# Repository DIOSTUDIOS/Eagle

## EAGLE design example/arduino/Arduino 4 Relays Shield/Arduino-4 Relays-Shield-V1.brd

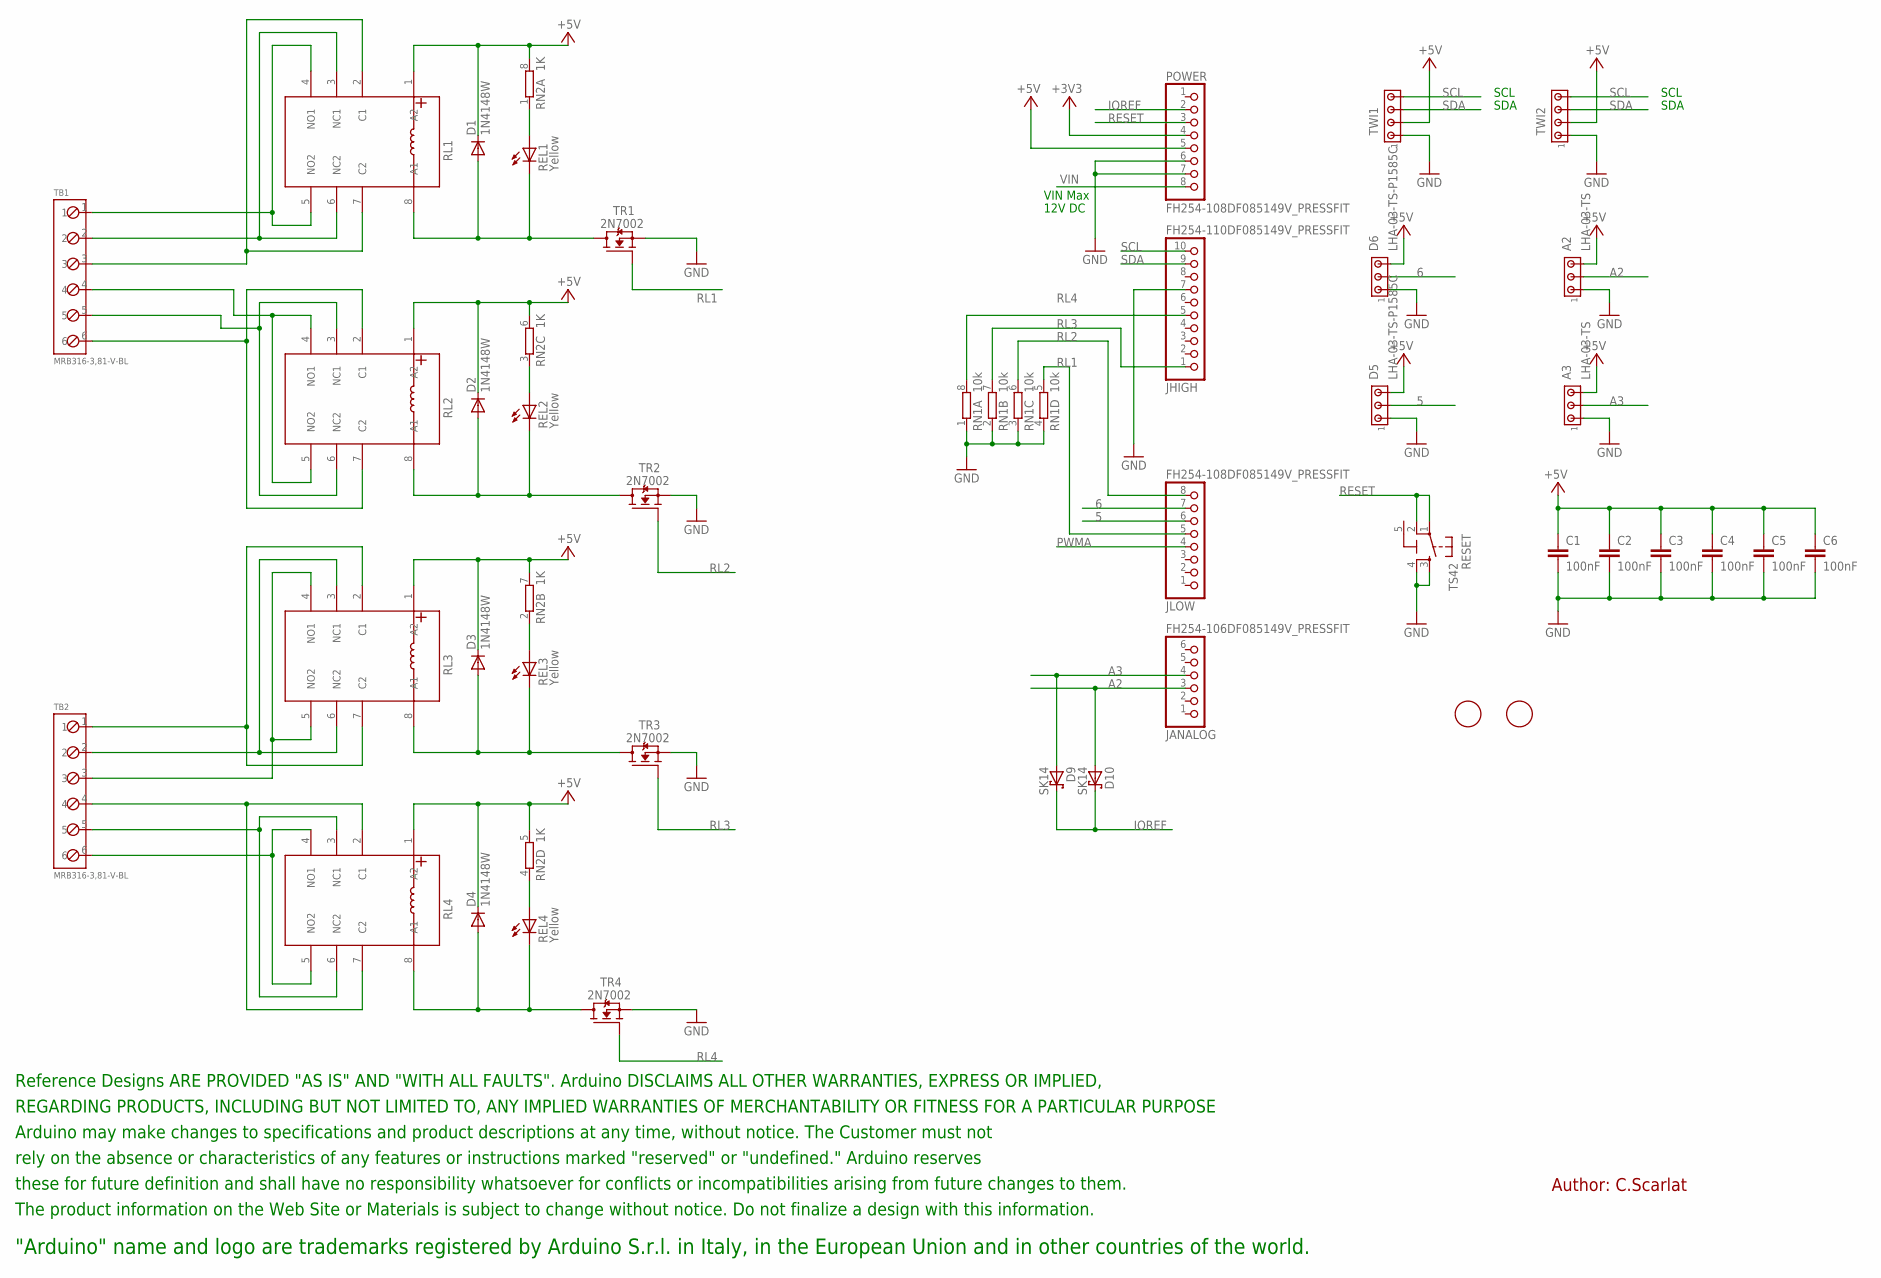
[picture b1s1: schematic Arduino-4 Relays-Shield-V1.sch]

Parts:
A2, A3: LHA-03-TS; 10X03MTA
C1, C2, C3, C4, C5, C6: 100nF; C0603-ROUND
D1, D2, D3, D4: 1N4148W; SOD123
D5, D6: LHA-03-TS-P1585C; 10X03MTA
D9, D10: SK14; SMB
FID2, FID3: FIDUCIALMOUNT; FIDUCIA-MOUNT
JANALOG: FH254-106DF085149V_PRESSFIT; 1X06-TH-PRESSFIT
JHIGH: FH254-110DF085149V_PRESSFIT; 1X10-TH-PRESSFIT
JLOW: FH254-108DF085149V_PRESSFIT; 1X08-TH-PRESSFIT
POWER: FH254-108DF085149V_PRESSFIT; 1X08-TH-PRESSFIT
REL1, REL2, REL3, REL4: Yellow; CHIPLED_0805
RESET: TS42
RL1, RL2, RL3, RL4: 1045_G5V-2-H1; RELE'-30SSERIES-DIL-2X
RN1: 10k; CAY16
RN2: 1K; CAY16
TB1, TB2: MRB316-3,81-V-BL
TR1, TR2, TR3, TR4: 2N7002; SOT-23
TWI1, TWI2: 0205_LHA-04-TS__4X1_VERTICALE_BIANCO_P_2,54; 10X04MTA
U$2: DISCLAIMER-SMALL; DISCLAIMER

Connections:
5: D5.2, JLOW.6
5-GND: RESET.5 (5-GND)
6: D6.2, JLOW.7
+3V3: POWER.4
+5V: A2.3, A3.3, C1.1, C2.1, C3.1, C4.1, C5.1, C6.1, D1.C, D2.C, D3.C, D4.C, D5.3, D6.3, POWER.5, RL1.1 (A2), RL2.1 (A2), RL3.1 (A2), RL4.1 (A2), RN2.5 (2), RN2.6 (2), RN2.7 (2), RN2.8 (2), TWI1.2, TWI2.2
A2: A2.2, D10.A, JANALOG.3
A3: A3.2, D9.A, JANALOG.4
GND: A2.1, A3.1, C1.2, C2.2, C3.2, C4.2, C5.2, C6.2, D5.1, D6.1, JHIGH.7, POWER.6, POWER.7, RESET.3, RESET.4, RN1.1, RN1.2 (1), RN1.3 (1), RN1.4 (1), TR1.2 (S), TR2.2 (S), TR3.2 (S), TR4.2 (S), TWI1.1, TWI2.1
IOREF: D9.C, D10.C, POWER.2
unnamed: REL1.A, RN2.1
unnamed: REL2.A, RN2.3 (1)
unnamed: REL3.A, RN2.2 (1)
unnamed: REL4.A, RN2.4 (1)
unnamed: D1.A, REL1.C, RL1.8 (A1), TR1.1 (D)
unnamed: D2.A, REL2.C, RL2.8 (A1), TR2.1 (D)
unnamed: D3.A, REL3.C, RL3.8 (A1), TR3.1 (D)
unnamed: D4.A, REL4.C, RL4.8 (A1), TR4.1 (D)
PWMA: JLOW.4
REL1_COM: RL1.2 (C1), RL1.7 (C2), TB1.3
REL1_NC: RL1.3 (NC1), RL1.6 (NC2), TB1.2
REL1_NO: RL1.4 (NO1), RL1.5 (NO2), TB1.1
REL2_COM: RL2.2 (C1), RL2.7 (C2), TB1.6
REL2_NC: RL2.3 (NC1), RL2.6 (NC2), TB1.5
REL2_NO: RL2.4 (NO1), RL2.5 (NO2), TB1.4
REL3_COM: RL3.2 (C1), RL3.7 (C2), TB2.1
REL3_NC: RL3.3 (NC1), RL3.6 (NC2), TB2.2
REL3_NO: RL3.4 (NO1), RL3.5 (NO2), TB2.3
REL4_COM: RL4.2 (C1), RL4.7 (C2), TB2.4
REL4_NC: RL4.3 (NC1), RL4.6 (NC2), TB2.5
REL4_NO: RL4.4 (NO1), RL4.5 (NO2), TB2.6
RESET: POWER.3, RESET.1, RESET.2
RL1: JLOW.5, RN1.5 (2), TR1.3 (G)
RL2: JLOW.8, RN1.6 (2), TR2.3 (G)
RL3: JHIGH.1, RN1.7 (2), TR3.3 (G)
RL4: JHIGH.5, RN1.8 (2), TR4.3 (G)
SCL: JHIGH.10, TWI1.4, TWI2.4
SDA: JHIGH.9, TWI1.3, TWI2.3
VIN: POWER.8

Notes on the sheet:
VIN Max
12V DC
SCL
SDA
Author: C.Scarlat

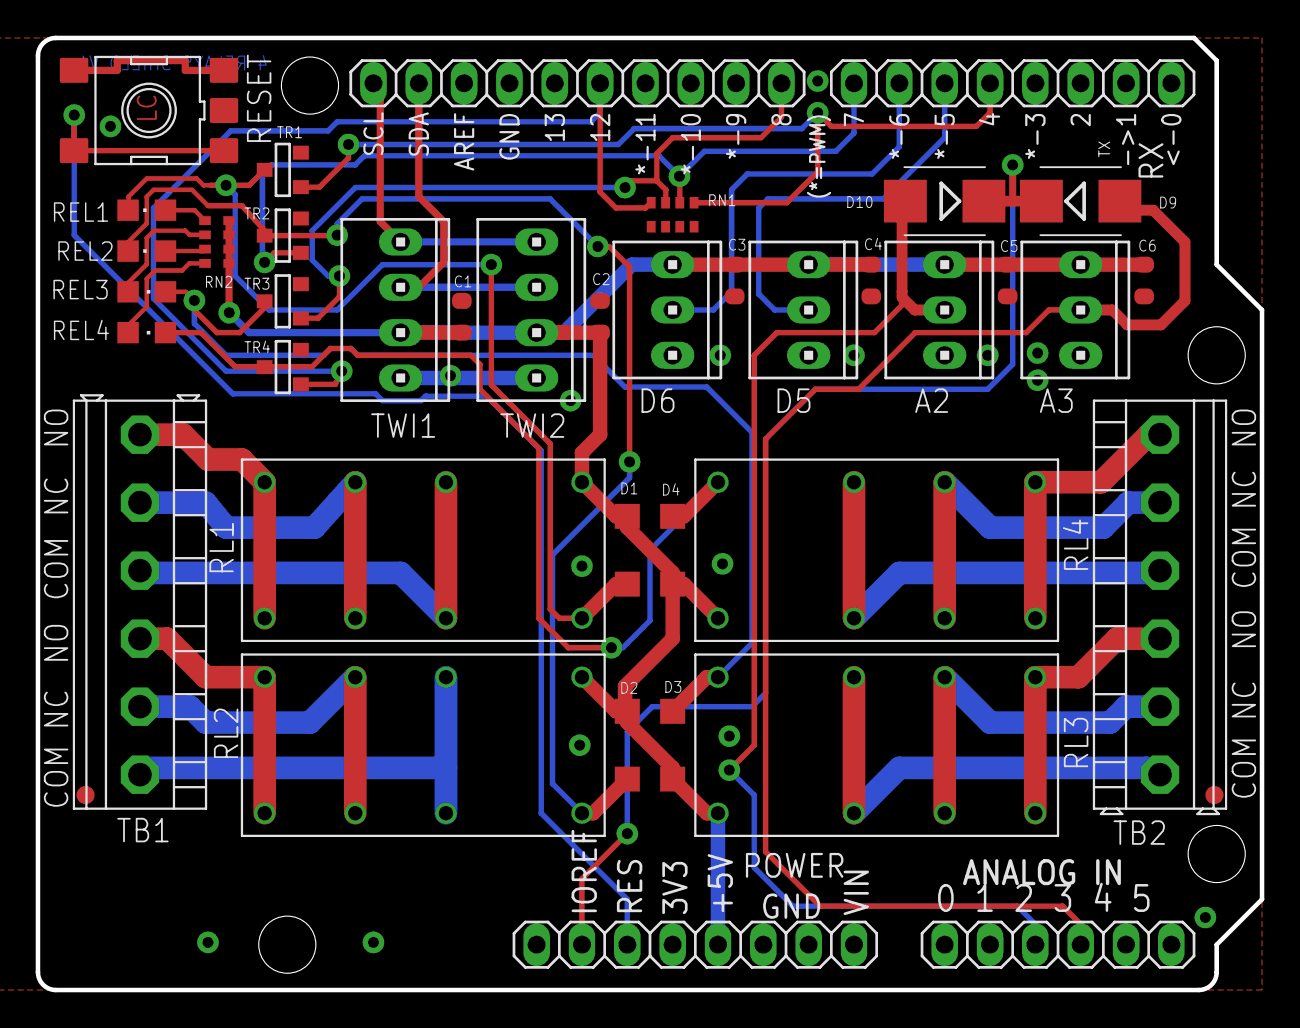
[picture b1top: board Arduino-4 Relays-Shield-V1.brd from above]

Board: 2 copper layers, 68.6 x 53.3 mm, 42 parts (0 on the bottom side), 34 nets.

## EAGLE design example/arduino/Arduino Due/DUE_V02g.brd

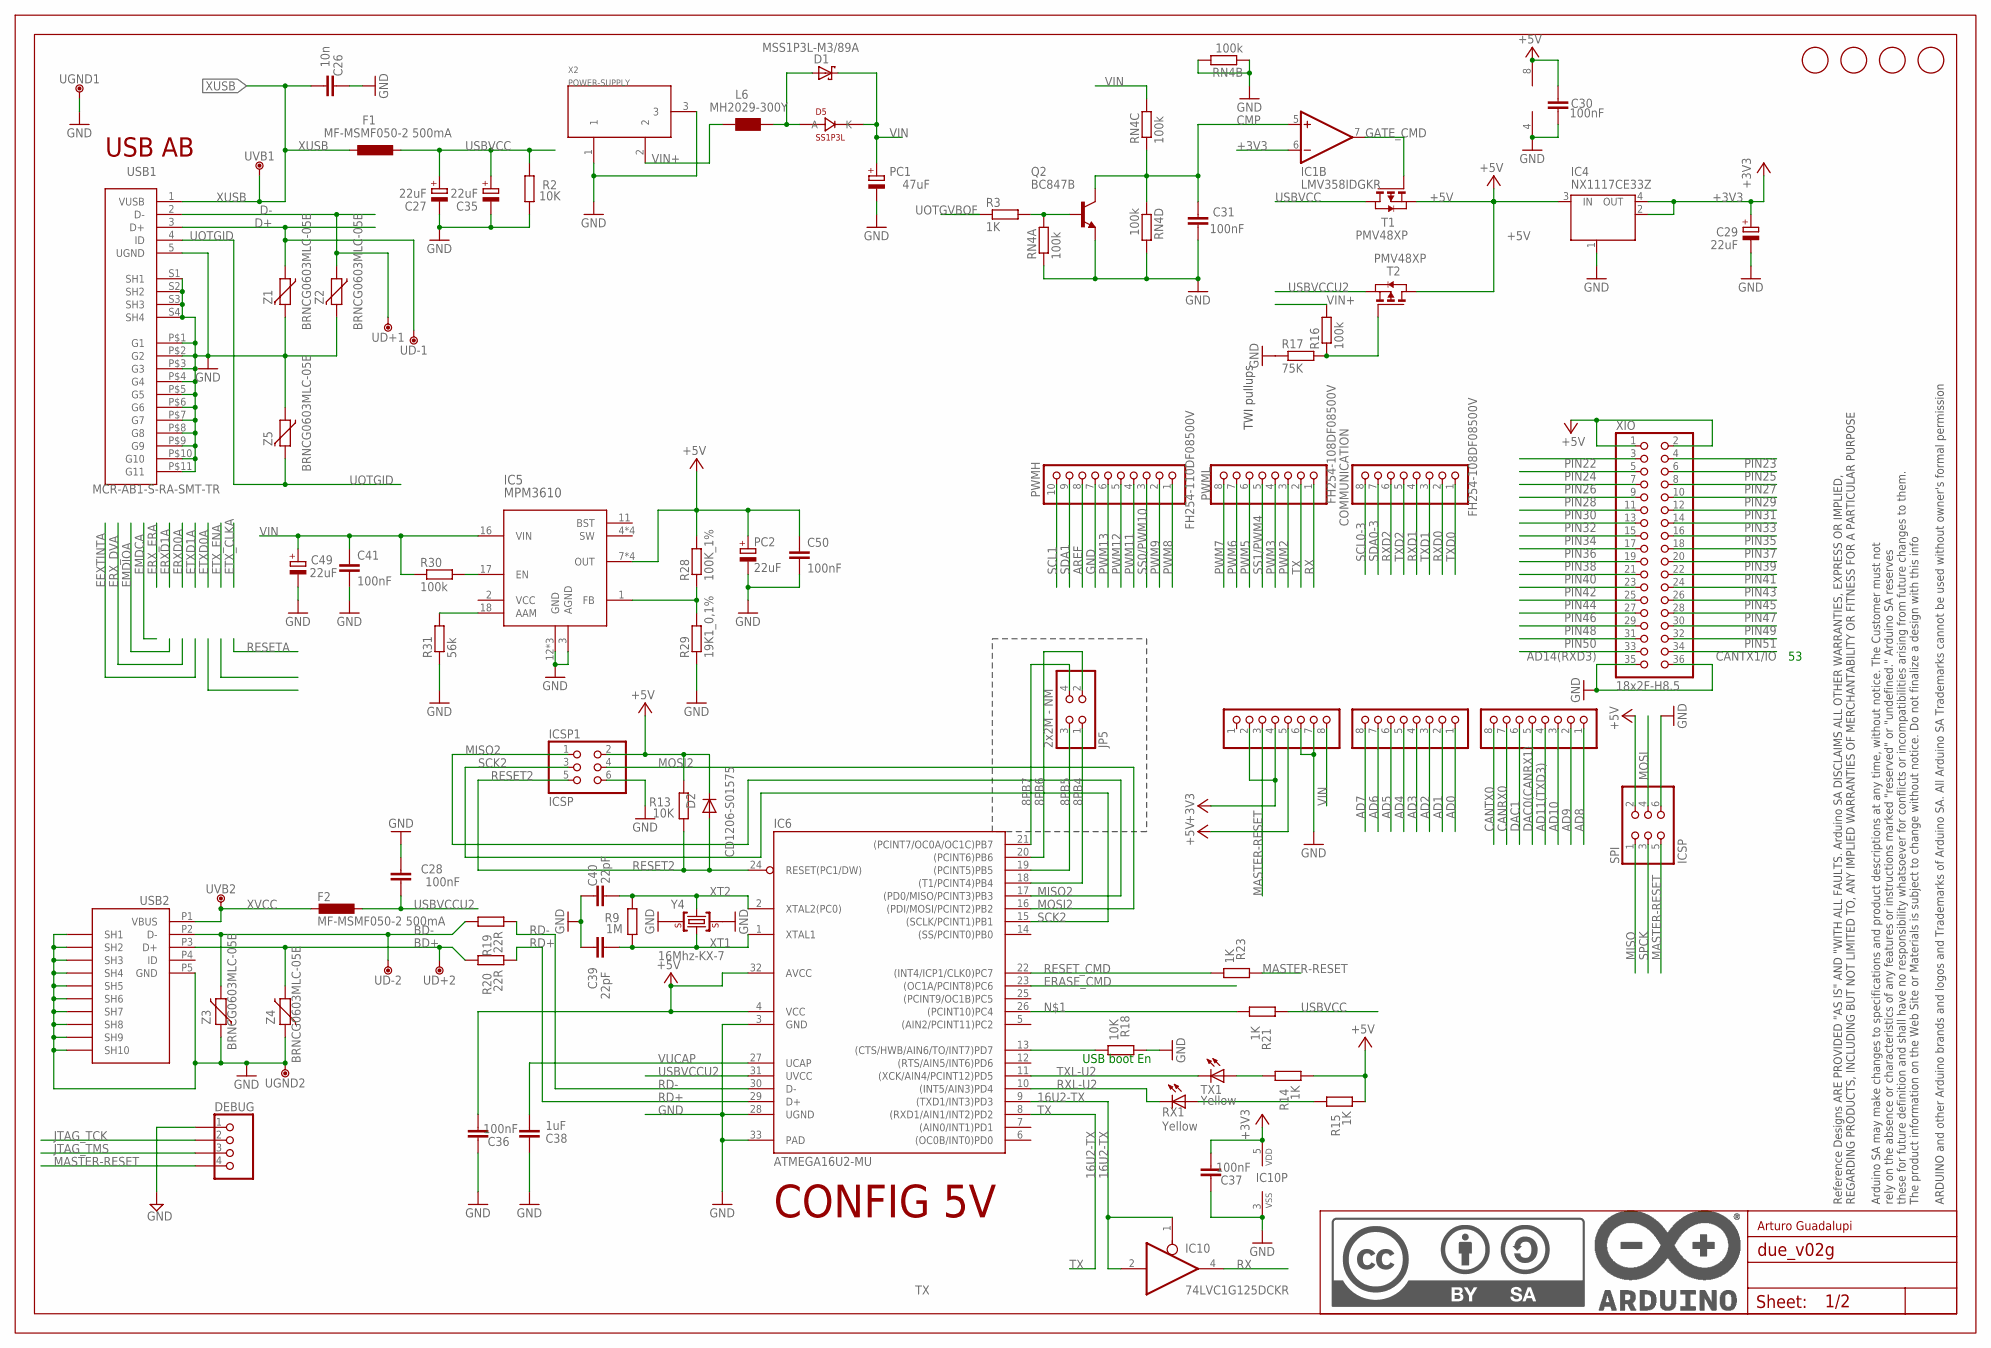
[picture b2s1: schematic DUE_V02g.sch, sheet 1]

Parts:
ADCH: FH254-108DF08500V; 1X08
ADCL: FH254-108DF08500V; 1X08
C26: 10n; C0402
C27, C29, C35, C49: 22uF; SMC_B
C28, C30, C31, C36, C37: 100nF; C0402
C38: 1uF; C0402
C39, C40: 22pF; C0402
C41, C50: 100nF; C0603-ROUND
COMMUNICATION: FH254-108DF08500V; 1X08
D1: MSS1P3L-M3/89A; MICROSMP
D2: CD1206-S01575; MINIMELF
D5: SS1P3L; DO220AAL
DEBUG: 0644_4X1VP.2,54H11,8; PH1X4-THT
F1, F2: MF-MSMF050-2 500mA; L1812
FID1, FID2, FID3, FID4: FIDUCIALMOUNT; FIDUCIA-MOUNT
IC1: LMV358IDGKR; MSOP08
IC4: NX1117CE33Z; SOT223
IC5: MPM3610; QFN-20
IC6: ATMEGA16U2-MU; MLF32
IC10: 74LVC1G125DCKR; SC70-5
ICSP1: ICSP; 2X03
JP5: 2x2M - NM; 2X02
L6: MH2029-300Y; 0805
PC1: 47uF; PANASONIC_D
PC2: 22uF; SMC_B
POWER: FH254-108DF08500V; 1X08
PWMH: FH254-110DF08500V; 1X10
PWML: FH254-108DF08500V; 1X08
Q2: BC847B; SOT23
R2, R13, R18: 10K; R0402
R3, R14, R15, R21, R23: 1K; R0402
R9: 1M; R0402
R16: 100k; R0402
R17: 75K; R0603-ROUND
R19, R20: 22R; R0402
R28: 100K_1%; R0603-ROUND
R29: 19K1_0,1%; R0603-ROUND
R30: 100k; R0603-ROUND
R31: 56k; R0603-ROUND
RN4: 100k; CAY16
RX1: Yellow; CHIPLED_0805
SPI: ICSP; 2X03
T1, T2: PMV48XP; SOT-23
TX1: Yellow; CHIPLED_0805
U$1: DNP; FRAME
UD+1, UD+2: DNP; TP-1.00MM
UD-1, UD-2: DNP; TP-1.00MM
UGND1, UGND2: DNP; TP-1.00MM
USB1: MCR-AB1-S-RA-SMT-TR; MCR-AB1-S-RA-SMT
USB2: MCR-B-S-RA-SMT-CS1TR; CON2_USB_MICRO_B_AT
UVB1, UVB2: DNP; TP-1.00MM
X2: POWER-SUPPLY; POWERSUPPLY_DC-21MM
XIO: 18x2F-H8.5; 2X18
Y4: 16Mhz-KX-7; CRYSTAL-3.2-2.5
Z1, Z2, Z3, Z4, Z5: BRNCG0603MLC-05E; CT/CN0603

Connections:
8PB4: IC6.18 ((T1/PCINT4)PB4), JP5.1
8PB5: IC6.19 ((PCINT5)PB5), JP5.3
8PB6: IC6.20 ((PCINT6)PB6), JP5.2
8PB7: IC6.21 ((PCINT7/OC0A/OC1C)PB7), JP5.4
16U2-TX: IC6.9 ((TXD1/INT3)PD3), IC10.1 (OE), IC10.2 (I)
+3V3: C29.+, C37.1, IC1.6 (-IN), IC4.2 (OUT), IC4.4 (OUT), IC10.5 (VDD), POWER.2, POWER.4; also elsewhere on the board
+5V: C30.2, C36.1, C50.1, D2.C, IC1.8 (V+), IC4.3 (IN), IC5.7 (OUT), IC5.8 (OUT), IC5.9 (OUT), IC5.20 (OUT), IC6.4 (VCC), IC6.32 (AVCC), ICSP1.2, PC2.+, POWER.5, R13.2, R14.1, R15.1, R28.2, SPI.2, T1.2 (S), T2.1 (D), XIO.1, XIO.2
AD0: ADCL.1; also elsewhere on the board
AD1: ADCL.2; also elsewhere on the board
AD2: ADCL.3; also elsewhere on the board
AD3: ADCL.4; also elsewhere on the board
AD4: ADCL.5; also elsewhere on the board
AD5: ADCL.6; also elsewhere on the board
AD6: ADCL.7; also elsewhere on the board
AD7: ADCL.8; also elsewhere on the board
AD8: ADCH.1; also elsewhere on the board
AD9: ADCH.2; also elsewhere on the board
AD10: ADCH.3; also elsewhere on the board
AD11(TXD3): ADCH.4; also elsewhere on the board
AD14(RXD3): XIO.33; also elsewhere on the board
AREF: PWMH.8; also elsewhere on the board
BD+: R20.2, UD+2.X, USB2.P3 (D+), Z4.2
BD-: R19.2, UD-2.X, USB2.P2 (D-), Z3.2
CANRX0: ADCH.7; also elsewhere on the board
CANTX0: ADCH.8; also elsewhere on the board
CANTX1/IO: XIO.34; also elsewhere on the board
CMP: C31.2, IC1.5 (+IN), Q2.3 (C), RN4.3 (1), RN4.4 (1)
D+: UD-1.X, USB1.3 (D+), Z1.1; also elsewhere on the board
D-: UD+1.X, USB1.2 (D-), Z2.1; also elsewhere on the board
DAC0(CANRX1): ADCH.5; also elsewhere on the board
DAC1: ADCH.6; also elsewhere on the board
DTR: IC6.13 ((CTS/HWB/AIN6/TO/INT7)PD7), R18.1
ERASE_CMD: IC6.23 ((OC1A/PCINT8)PC6); also elsewhere on the board
GATE_CMD: IC1.7 (OUT), T1.3 (G)
GND: C26.2, C27.-, C28.2, C29.-, C30.1, C31.1, C35.-, C36.2, C37.2, C38.2, C39.2, C40.2, C41.2, C49.-, C50.2, DEBUG.1, IC1.4 (V-), IC4.1 (GND/ADJ), IC5.3 (AGND), IC5.12 (GND), IC5.13 (GND), IC5.14 (GND), IC6.3 (GND), IC6.28 (UGND), IC6.33 (PAD), IC10.3 (VSS), ICSP1.6, PC1.-, PC2.-, POWER.6, POWER.7, PWMH.7, Q2.2 (E), R2.1, R17.1, R18.2, R29.1, R31.1, RN4.1, RN4.2 (1), RN4.5 (2), RN4.7 (2), SPI.6, UGND1.X, UGND2.X, USB1.5 (UGND), USB1.P$1 (G1), USB1.P$2 (G2), USB1.P$3 (G3), USB1.P$4 (G4), USB1.P$5 (G5), USB1.P$6 (G6), USB1.P$7 (G7), USB1.P$8 (G8), USB1.P$9 (G9), USB1.P$10 (G10), USB1.P$11 (G11), USB1.S1 (SH1), USB1.S2 (SH2), USB1.S3 (SH3), USB1.S4 (SH4), USB2.P5 (GND), USB2.P$1 (SH7), USB2.P$2 (SH8), USB2.P$3 (SH9), USB2.P$4 (SH10), USB2.P$5 (SH7), USB2.P$6 (SH8), USB2.P$7 (SH9), USB2.P$8 (SH10), USB2.S1 (SH1), USB2.S2 (SH2), USB2.S3 (SH3), USB2.S4 (SH4), USB2.S5 (SH5), USB2.S6 (SH6), X2.1, X2.3, XIO.35, XIO.36, Y4.2 (GND), Y4.4 (GND), Z1.2, Z2.2, Z3.1, Z4.1, Z5.1; also elsewhere on the board
JTAG_TCK: DEBUG.2; also elsewhere on the board
JTAG_TMS: DEBUG.3; also elsewhere on the board
MASTER-RESET: DEBUG.4, POWER.3, R23.2, SPI.5; also elsewhere on the board
MISO: SPI.1; also elsewhere on the board
MISO2: IC6.17 ((PD0/MISO/PCINT3)PB3), ICSP1.1
MOSI: SPI.4; also elsewhere on the board
MOSI2: IC6.16 ((PDI/MOSI/PCINT2)PB2), ICSP1.4
unnamed: IC6.26 ((PCINT10)PC4), R21.1
unnamed: R15.2, RX1.A
unnamed: Q2.1 (B), R3.2, RN4.8 (2)
unnamed: D1.A, D5.P$2 (A), L6.1
unnamed: R14.2, TX1.A
unnamed: R16.1, R17.2, T2.3 (G)
unnamed: IC5.1 (FB), R28.1, R29.2
unnamed: IC5.17 (EN), R30.2
unnamed: IC5.18 (AAM), R31.2
PIN22: XIO.3; also elsewhere on the board
PIN23: XIO.4; also elsewhere on the board
PIN24: XIO.5; also elsewhere on the board
PIN25: XIO.6; also elsewhere on the board
PIN26: XIO.7; also elsewhere on the board
PIN27: XIO.8; also elsewhere on the board
PIN28: XIO.9; also elsewhere on the board
PIN29: XIO.10; also elsewhere on the board
PIN30: XIO.11; also elsewhere on the board
PIN31: XIO.12; also elsewhere on the board
PIN32: XIO.13; also elsewhere on the board
PIN33: XIO.14; also elsewhere on the board
PIN34: XIO.15; also elsewhere on the board
PIN35: XIO.16; also elsewhere on the board
PIN36: XIO.17; also elsewhere on the board
PIN37: XIO.18; also elsewhere on the board
PIN38: XIO.19; also elsewhere on the board
PIN39: XIO.20; also elsewhere on the board
PIN40: XIO.21; also elsewhere on the board
PIN41: XIO.22; also elsewhere on the board
PIN42: XIO.23; also elsewhere on the board
PIN43: XIO.24; also elsewhere on the board
PIN44: XIO.25; also elsewhere on the board
PIN45: XIO.26; also elsewhere on the board
PIN46: XIO.27; also elsewhere on the board
PIN47: XIO.28; also elsewhere on the board
PIN48: XIO.29; also elsewhere on the board
PIN49: XIO.30; also elsewhere on the board
PIN50: XIO.31; also elsewhere on the board
PIN51: XIO.32; also elsewhere on the board
PWM2: PWML.3; also elsewhere on the board
PWM3: PWML.4; also elsewhere on the board
PWM5: PWML.6; also elsewhere on the board
PWM6: PWML.7; also elsewhere on the board
PWM7: PWML.8; also elsewhere on the board
PWM8: PWMH.1; also elsewhere on the board
PWM9: PWMH.2; also elsewhere on the board
PWM11: PWMH.4; also elsewhere on the board
PWM12: PWMH.5; also elsewhere on the board
PWM13: PWMH.6; also elsewhere on the board
RD+: IC6.29 (D+), R20.1
RD-: IC6.30 (D-), R19.1
RESET2: D2.A, IC6.24 (RESET(PC1/DW)), ICSP1.5, R13.1
RESET_CMD: IC6.22 ((INT4/ICP1/CLK0)PC7), R23.1
RX: IC10.4 (O), PWML.1; also elsewhere on the board
RXD0: COMMUNICATION.2; also elsewhere on the board
RXD1: COMMUNICATION.4; also elsewhere on the board
RXD2: COMMUNICATION.6; also elsewhere on the board
RXL-U2: IC6.10 ((INT5/AIN3)PD4), RX1.C
SCK2: IC6.15 ((SCLK/PCINT1)PB1), ICSP1.3
SCL0-3: COMMUNICATION.8; also elsewhere on the board
SCL1: PWMH.10; also elsewhere on the board
SDA0-3: COMMUNICATION.7; also elsewhere on the board
SDA1: PWMH.9; also elsewhere on the board
SPCK: SPI.3; also elsewhere on the board
SS0/PWM10: PWMH.3; also elsewhere on the board
SS1/PWM4: PWML.5; also elsewhere on the board
TX: IC6.8 ((RXD1/AIN1/INT2)PD2), PWML.2; also elsewhere on the board
TXD0: COMMUNICATION.1; also elsewhere on the board
TXD1: COMMUNICATION.3; also elsewhere on the board
TXD2: COMMUNICATION.5; also elsewhere on the board
TXL-U2: IC6.11 ((XCK/AIN4/PCINT12)PD5), TX1.C
UOTGID: USB1.4 (ID), Z5.2; also elsewhere on the board
UOTGVBOF: R3.1; also elsewhere on the board
USBVCC: C27.+, C35.+, F1.1, R2.2, R21.2, T1.1 (D)
USBVCCU2: C28.1, F2.1, IC6.31 (UVCC), T2.2 (S)
VIN: C41.1, C49.+, D1.K (C), D5.P$1 (K), IC5.16 (VIN), PC1.+, POWER.8, R30.1, RN4.6 (2)
VIN+: L6.2, R16.2, X2.2
VUCAP: C38.1, IC6.27 (UCAP)
XT1: C39.1, IC6.1 (XTAL1), R9.1, Y4.1 (C1)
XT2: C40.1, IC6.2 (XTAL2(PC0)), R9.2, Y4.3 (C2)
XUSB: C26.1, F1.2, USB1.1 (VUSB), UVB1.X; also elsewhere on the board
XVCC: F2.2, USB2.P1 (VBUS), UVB2.X

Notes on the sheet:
TWI pullups
USB AB
USB boot En
CONFIG 5V
Arturo Guadalupi

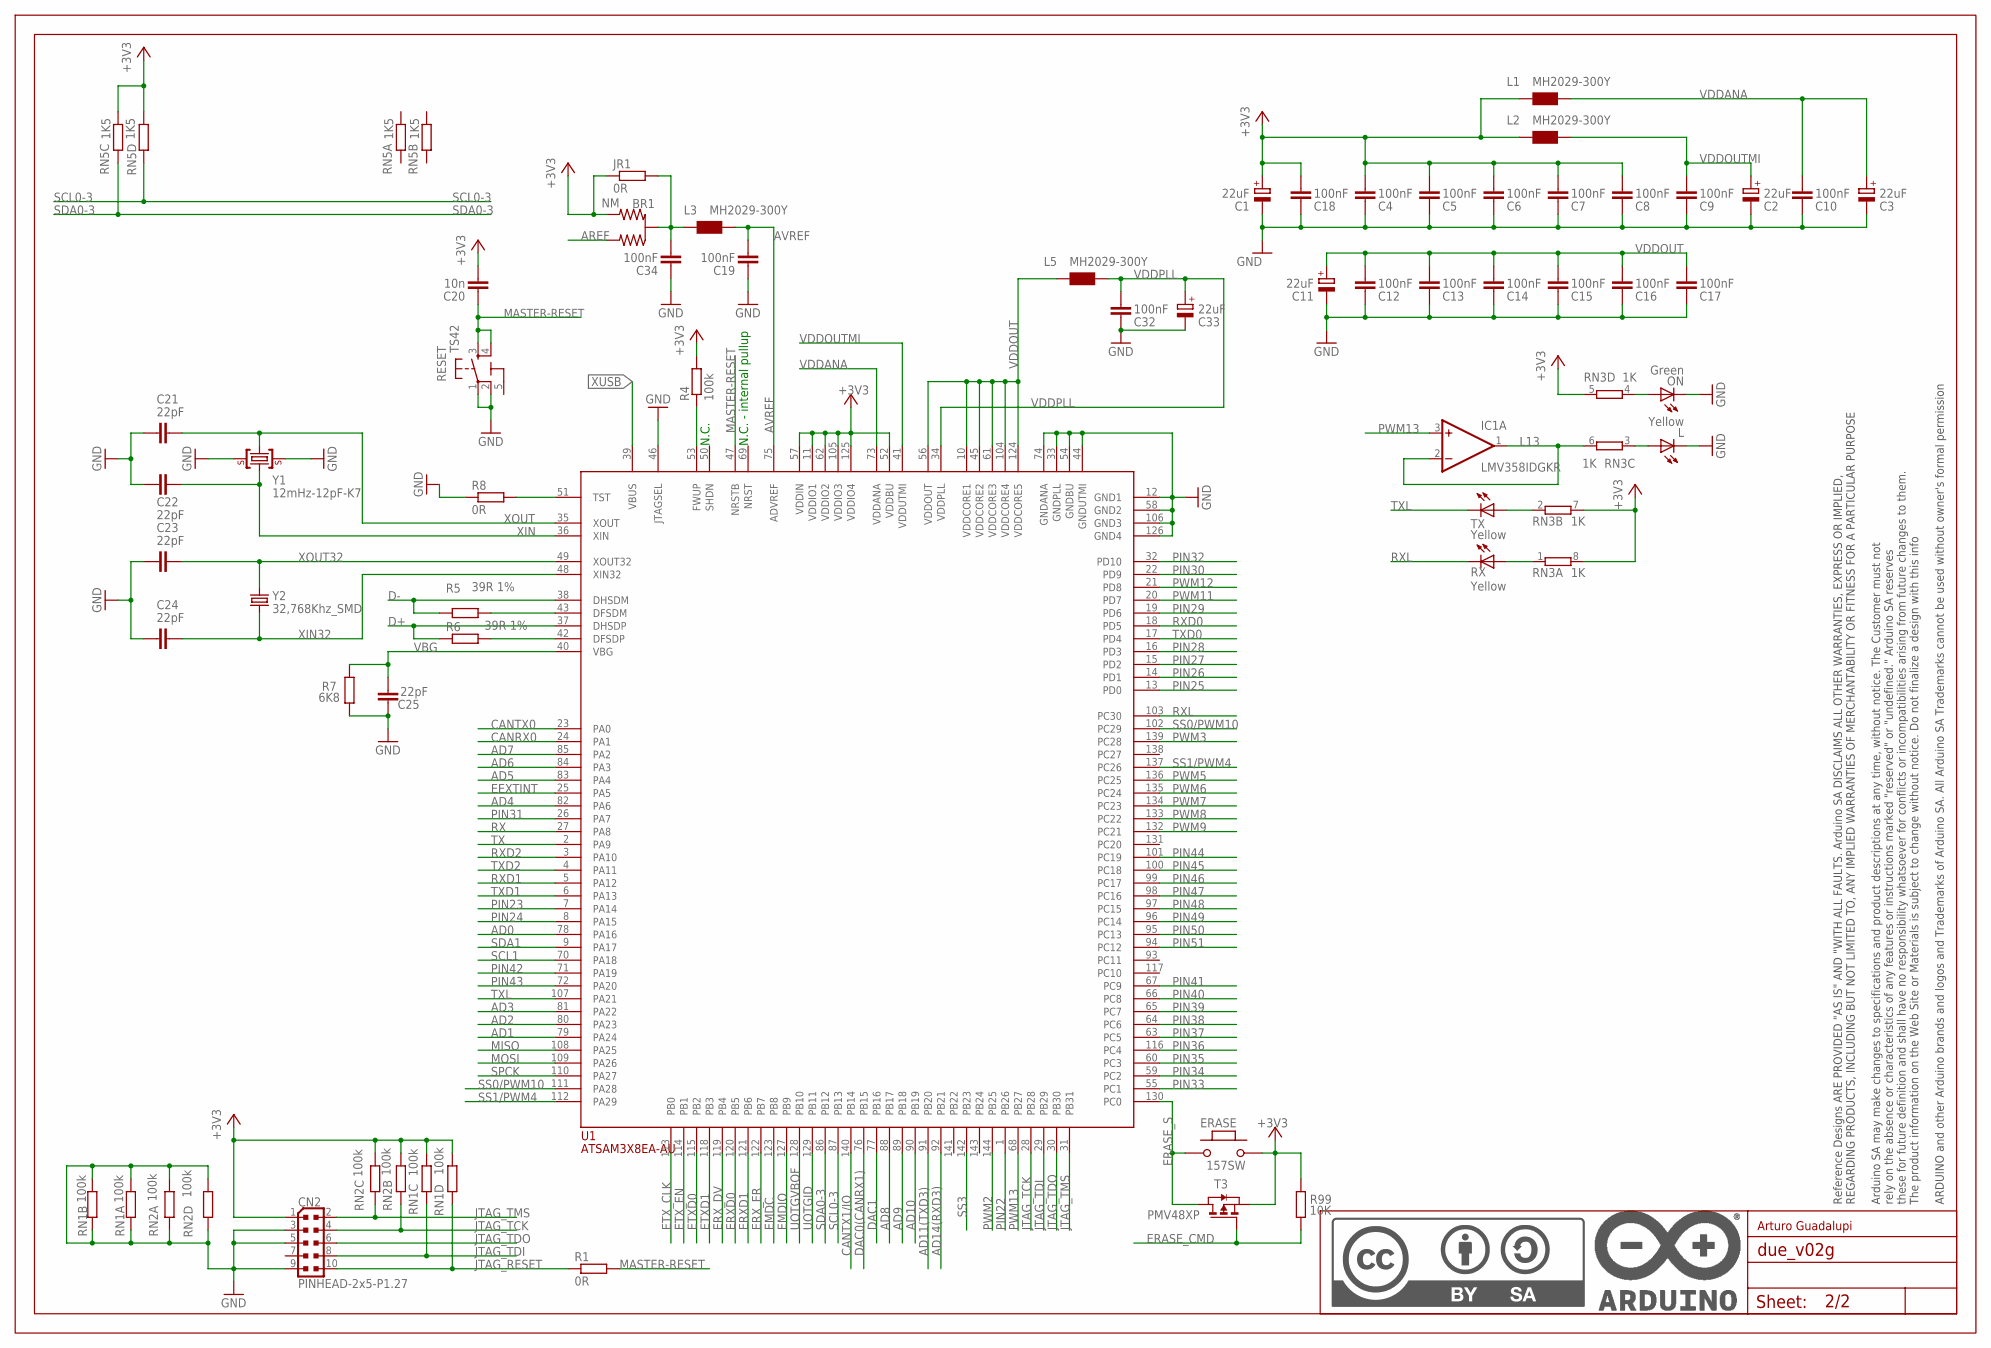
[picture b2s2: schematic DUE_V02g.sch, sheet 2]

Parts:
BR1: NM; J0402
C1, C2, C3, C11, C33: 22uF; SMC_B
C4, C5, C6, C7, C8, C9, C10, C12, C13, C14, C15, C16, C17, C18, C19, C32, C34: 100nF; C0402
C20: 10n; C0402
C21, C22, C23, C24, C25: 22pF; C0402
CN2: PINHEAD-2x5-P1.27; PINHEAD_2X05_127
ERASE: 157SW; SMD_157SW
IC1: LMV358IDGKR; MSOP08
JR1: 0R; R0402
L: Yellow; CHIPLED_0805
L1, L2, L3, L5: MH2029-300Y; 0805
ON: Green; CHIPLED_0805
R1, R8: 0R; R0402
R4: 100k; R0402
R5, R6: 39R 1%; R0402
R7: 6K8; R0603-ROUND
R99: 10K; R0402
RESET: TS42
RN1, RN2: 100k; CAY16
RN3: 1K; CAY16
RN5: 1K5; CAY16
RX: Yellow; CHIPLED_0805
T3: PMV48XP; SOT-23
TX: Yellow; CHIPLED_0805
U1: ATSAM3X8EA-AU; LQFP144
U$2: DNP; FRAME
Y1: 12mHz-12pF-K7; CRYSTAL-3.2-2.5
Y2: 32,768Khz_SMD; RESONATOR_EPSON_FC_145

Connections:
5-GND: RESET.5 (5-GND)
+3V3: BR1.3 (2), C1.+, C4.2, C5.2, C6.2, C7.2, C8.2, C18.2, C20.2, CN2.1, ERASE.1, JR1.1, L1.1, L2.1, R4.2, R99.2, RN1.5 (2), RN1.6 (2), RN2.2 (1), RN2.3 (1), RN3.5 (2), RN3.7 (2), RN3.8 (2), RN5.3 (1), RN5.4 (1), T3.2 (S), U1.11 (VDDIO1), U1.52 (VDDBU), U1.57 (VDDIN), U1.62 (VDDIO2), U1.105 (VDDIO3), U1.125 (VDDIO4); also elsewhere on the board
AD0: U1.78 (PA16); also elsewhere on the board
AD1: U1.79 (PA24); also elsewhere on the board
AD2: U1.80 (PA23); also elsewhere on the board
AD3: U1.81 (PA22); also elsewhere on the board
AD4: U1.82 (PA6); also elsewhere on the board
AD5: U1.83 (PA4); also elsewhere on the board
AD6: U1.84 (PA3); also elsewhere on the board
AD7: U1.85 (PA2); also elsewhere on the board
AD8: U1.88 (PB17); also elsewhere on the board
AD9: U1.89 (PB18); also elsewhere on the board
AD10: U1.90 (PB19); also elsewhere on the board
AD11(TXD3): U1.91 (PB20); also elsewhere on the board
AD14(RXD3): U1.92 (PB21); also elsewhere on the board
AREF: BR1.1; also elsewhere on the board
AVREF: C19.2, L3.2, U1.75 (ADVREF)
AVREFL: BR1.2 (C), C34.2, JR1.2, L3.1
CANRX0: U1.24 (PA1); also elsewhere on the board
CANTX0: U1.23 (PA0); also elsewhere on the board
CANTX1/IO: U1.140 (PB14); also elsewhere on the board
D+: R6.1, U1.37 (DHSDP); also elsewhere on the board
D-: R5.1, U1.38 (DHSDM); also elsewhere on the board
DAC0(CANRX1): U1.76 (PB15); also elsewhere on the board
DAC1: U1.77 (PB16); also elsewhere on the board
EEXTINT: U1.25 (PA5)
EMDC: U1.123 (PB8)
EMDIO: U1.127 (PB9)
ERASE_CMD: R99.1, T3.3 (G); also elsewhere on the board
ERASE_S: ERASE.2, T3.1 (D), U1.130 (PC0)
ERXD0: U1.120 (PB5)
ERXD1: U1.121 (PB6)
ERX_DV: U1.119 (PB4)
ERX_ER: U1.122 (PB7)
ETXD0: U1.115 (PB2)
ETXD1: U1.118 (PB3)
ETX_CLK: U1.113 (PB0)
ETX_EN: U1.114 (PB1)
GND: C1.-, C2.-, C3.-, C4.1, C5.1, C6.1, C7.1, C8.1, C9.1, C10.1, C11.-, C12.1, C13.1, C14.1, C15.1, C16.1, C17.1, C18.1, C19.1, C21.2, C22.2, C23.2, C24.2, C25.2, C32.1, C33.-, C34.1, CN2.3, CN2.5, CN2.9, L.C, ON.C, R7.1, R8.1, RESET.1, RESET.2, RN1.1, RN1.2 (1), RN1.7 (2), RN1.8 (2), RN2.1, RN2.4 (1), RN2.5 (2), RN2.8 (2), U1.12 (GND1), U1.33 (GNDPLL), U1.44 (GNDUTMI), U1.46 (JTAGSEL), U1.54 (GNDBU), U1.58 (GND2), U1.74 (GNDANA), U1.106 (GND3), U1.126 (GND4), Y1.2 (GND), Y1.4 (GND); also elsewhere on the board
JTAG_RESET: CN2.10, R1.1, RN1.4 (1)
JTAG_TCK: CN2.4, RN2.7 (2), U1.28 (PB28); also elsewhere on the board
JTAG_TDI: CN2.8, RN1.3 (1), U1.29 (PB29)
JTAG_TDO: CN2.6, U1.30 (PB30)
JTAG_TMS: CN2.2, RN2.6 (2), U1.31 (PB31); also elsewhere on the board
L13: IC1.1 (OUT), IC1.2 (-IN), RN3.6 (2)
MASTER-RESET: C20.1, R1.2, RESET.3, RESET.4, U1.47 (NRSTB); also elsewhere on the board
MISO: U1.108 (PA25); also elsewhere on the board
MOSI: U1.109 (PA26); also elsewhere on the board
unnamed: L.A, RN3.3 (1)
unnamed: ON.A, RN3.4 (1)
unnamed: R8.2, U1.51 (TST)
unnamed: R4.1, U1.53 (FWUP)
unnamed: R5.2, U1.43 (DFSDM)
unnamed: R6.2, U1.42 (DFSDP)
unnamed: RN3.1, RX.A
unnamed: RN3.2 (1), TX.A
PIN22: U1.1 (PB26); also elsewhere on the board
PIN23: U1.7 (PA14); also elsewhere on the board
PIN24: U1.8 (PA15); also elsewhere on the board
PIN25: U1.13 (PD0); also elsewhere on the board
PIN26: U1.14 (PD1); also elsewhere on the board
PIN27: U1.15 (PD2); also elsewhere on the board
PIN28: U1.16 (PD3); also elsewhere on the board
PIN29: U1.19 (PD6); also elsewhere on the board
PIN30: U1.22 (PD9); also elsewhere on the board
PIN31: U1.26 (PA7); also elsewhere on the board
PIN32: U1.32 (PD10); also elsewhere on the board
PIN33: U1.55 (PC1); also elsewhere on the board
PIN34: U1.59 (PC2); also elsewhere on the board
PIN35: U1.60 (PC3); also elsewhere on the board
PIN36: U1.116 (PC4); also elsewhere on the board
PIN37: U1.63 (PC5); also elsewhere on the board
PIN38: U1.64 (PC6); also elsewhere on the board
PIN39: U1.65 (PC7); also elsewhere on the board
PIN40: U1.66 (PC8); also elsewhere on the board
PIN41: U1.67 (PC9); also elsewhere on the board
PIN42: U1.71 (PA19); also elsewhere on the board
PIN43: U1.72 (PA20); also elsewhere on the board
PIN44: U1.101 (PC19); also elsewhere on the board
PIN45: U1.100 (PC18); also elsewhere on the board
PIN46: U1.99 (PC17); also elsewhere on the board
PIN47: U1.98 (PC16); also elsewhere on the board
PIN48: U1.97 (PC15); also elsewhere on the board
PIN49: U1.96 (PC14); also elsewhere on the board
PIN50: U1.95 (PC13); also elsewhere on the board
PIN51: U1.94 (PC12); also elsewhere on the board
PWM2: U1.144 (PB25); also elsewhere on the board
PWM3: U1.139 (PC28); also elsewhere on the board
PWM5: U1.136 (PC25); also elsewhere on the board
PWM6: U1.135 (PC24); also elsewhere on the board
PWM7: U1.134 (PC23); also elsewhere on the board
PWM8: U1.133 (PC22); also elsewhere on the board
PWM9: U1.132 (PC21); also elsewhere on the board
PWM11: U1.20 (PD7); also elsewhere on the board
PWM12: U1.21 (PD8); also elsewhere on the board
PWM13: IC1.3 (+IN), U1.68 (PB27); also elsewhere on the board
RX: U1.27 (PA8); also elsewhere on the board
RXD0: U1.18 (PD5); also elsewhere on the board
RXD1: U1.5 (PA12); also elsewhere on the board
RXD2: U1.3 (PA10); also elsewhere on the board
RXL: RX.C, U1.103 (PC30)
SCL0-3: RN5.5 (2), U1.87 (PB13); also elsewhere on the board
SCL1: U1.70 (PA18); also elsewhere on the board
SDA0-3: RN5.6 (2), U1.86 (PB12); also elsewhere on the board
SDA1: U1.9 (PA17); also elsewhere on the board
SPCK: U1.110 (PA27); also elsewhere on the board
SS0/PWM10: U1.102 (PC29), U1.111 (PA28); also elsewhere on the board
SS1/PWM4: U1.112 (PA29), U1.137 (PC26); also elsewhere on the board
SS3: U1.142 (PB23)
TX: U1.2 (PA9); also elsewhere on the board
TXD0: U1.17 (PD4); also elsewhere on the board
TXD1: U1.6 (PA13); also elsewhere on the board
TXD2: U1.4 (PA11); also elsewhere on the board
TXL: TX.C, U1.107 (PA21)
UOTGID: U1.129 (PB11); also elsewhere on the board
UOTGVBOF: U1.128 (PB10); also elsewhere on the board
VBG: C25.1, R7.2, U1.40 (VBG)
VDDANA: C3.+, C10.2, L1.2, U1.73 (VDDANA)
VDDOUT: C11.+, C12.2, C13.2, C14.2, C15.2, C16.2, C17.2, L5.1, U1.10 (VDDCORE1), U1.45 (VDDCORE2), U1.56 (VDDOUT), U1.61 (VDDCORE3), U1.104 (VDDCORE4), U1.124 (VDDCORE5)
VDDOUTMI: C2.+, C9.2, L2.2, U1.41 (VDDUTMI)
VDDPLL: C32.2, C33.+, L5.2, U1.34 (VDDPLL)
XIN: C22.1, U1.36 (XIN), Y1.1 (C1)
XIN32: C24.1, U1.48 (XIN32), Y2.P$2 (2)
XOUT: C21.1, U1.35 (XOUT), Y1.3 (C2)
XOUT32: C23.1, U1.49 (XOUT32), Y2.P$1 (1)
XUSB: U1.39 (VBUS); also elsewhere on the board

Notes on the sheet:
N.C.
N.C. - internal pullup
Arturo Guadalupi

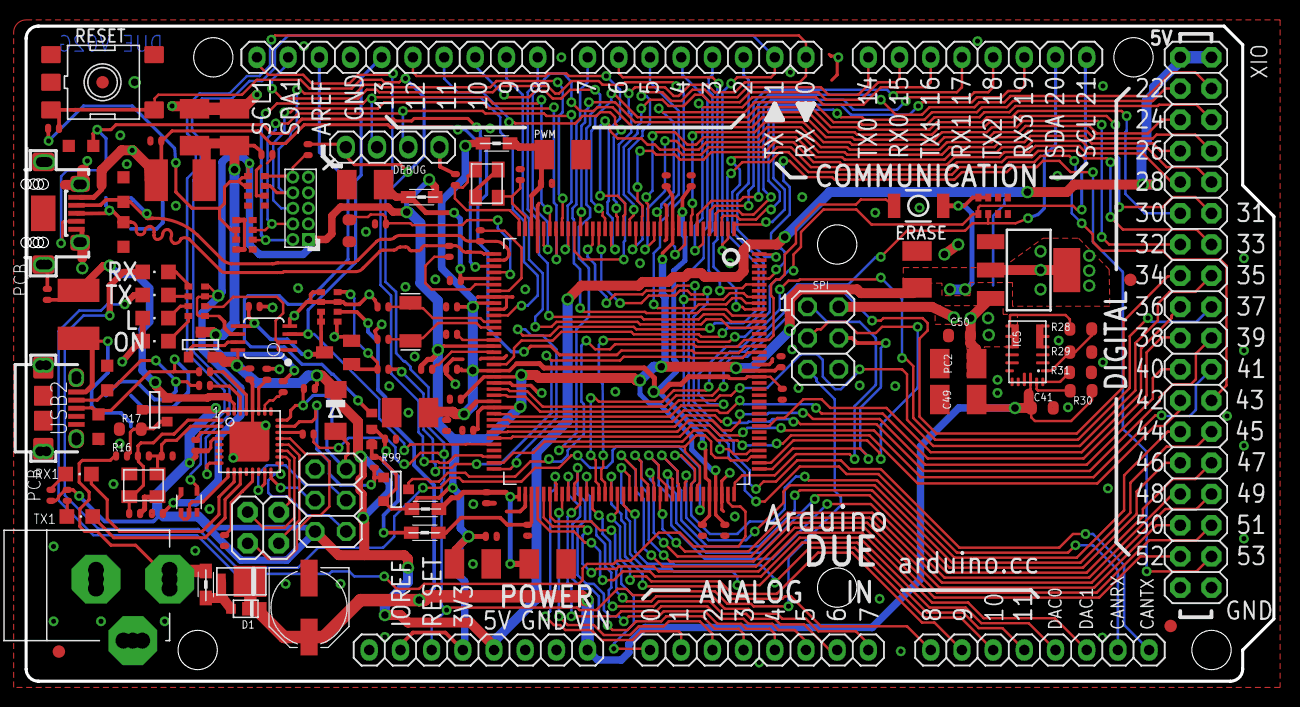
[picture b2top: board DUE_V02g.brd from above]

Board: 2 copper layers, 101.6 x 53.3 mm, 141 parts (0 on the bottom side), 150 nets.

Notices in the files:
example/arduino/Arduino MKR CAN Shield/MKRCANShieldV2.0.brd:
Copyright (c) 2016-2017 Arduino LLC.  All right reserved. EAGLE Design Rules
parts and their libraries:
Arduino-utility: Copyright (c) 2016-2017 Arduino LLC.  All right reserved.
Arduino-utility: This file is licensed under : CC-SA-BY-NC
cap-pan40: Copyright (C) 2004, Bob Starr
